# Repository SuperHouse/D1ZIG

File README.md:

D1 Mini Zigbee Shield
=====================

Zigbee shield for Wemos D1 Mini, so that it can either be a Zigbee
Client or a Zigbee Coordinator running Zigbee2Tasmota.

Features:

 * ESP8266 to run Zigbee2Tasmota
 * CC2530 Zigbee interface
 * 3D-printable case

More information is available at:

  https://www.superhouse.tv/d1zig

Hardware
--------
The "Hardware" directory contains the PCB design as an EAGLE project.
EAGLE PCB design software is available from Autodesk free for
non-commercial use.

Credits
-------
 * Jonathan Oxer <jon@oxer.com.au>

License
-------
Copyright 2020 SuperHouse Automation Pty Ltd  www.superhouse.tv  

The hardware portion of this project is licensed under the TAPR Open
Hardware License (www.tapr.org/OHL). The "license" folder within this
repository contains a copy of this license in plain text format.

The software portion of this project is licensed under the Simplified
BSD License. The "licence" folder within this project contains a
copy of this license in plain text format.

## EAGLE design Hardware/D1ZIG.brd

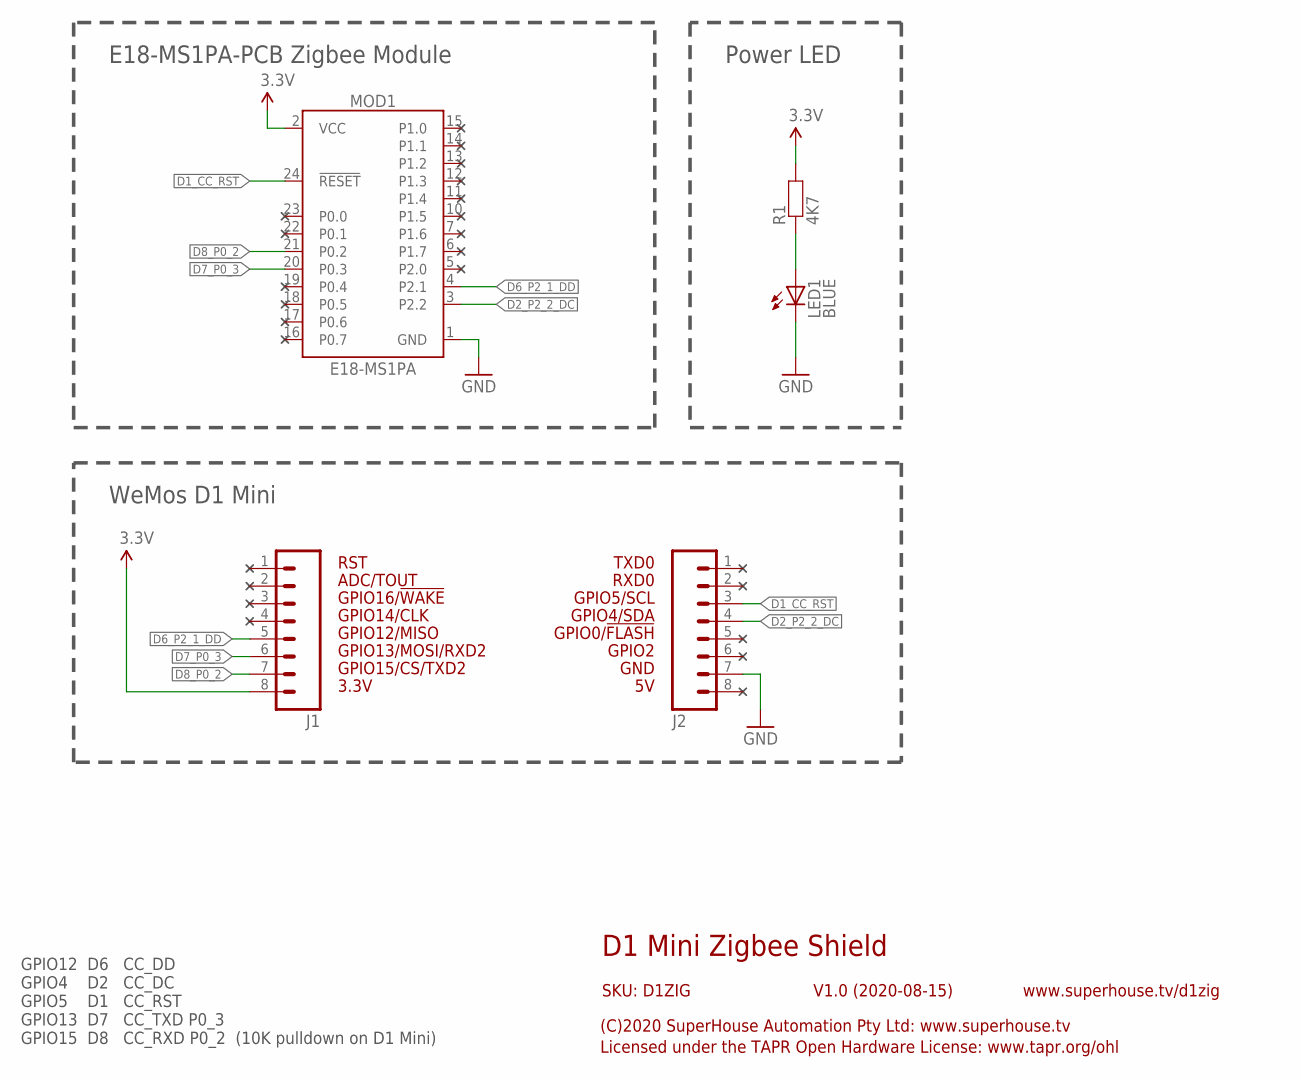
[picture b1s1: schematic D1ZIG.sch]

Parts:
J1, J2: M08; 1X08
LED1: BLUE; LED-0603
MOD1: E18-MS1PA; E18-MS1PA-PCB
R1: 4K7; R0603

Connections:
3.3V: J1.8, MOD1.2 (VCC), R1.2
D1_CC_RST: J2.3, MOD1.24 (!RESET)
D2_P2_2_DC: J2.4, MOD1.3 (P2.2)
D6_P2_1_DD: J1.5, MOD1.4 (P2.1)
D7_P0_3: J1.6, MOD1.20 (P0.3)
D8_P0_2: J1.7, MOD1.21 (P0.2)
GND: J2.7, LED1.C, MOD1.1 (GND)
unnamed: LED1.A, R1.1

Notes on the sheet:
GPIO2
GPIO0/!FLASH
GPIO12/MISO
GPIO4/SDA
GPIO5/SCL
RXD0
TXD0
GPIO13/MOSI/RXD2
GPIO14/CLK
GPIO15/CS/TXD2
GPIO16/!WAKE
ADC/TOUT
GPIO12 D6 CC_DD GPIO4 D2 CC_DC GPIO5 D1 CC_RST GPIO13 D7 CC_TXD P0_3 GPIO15 D8 CC_RXD P0_2 (10K pulldown on D1 Mini)
GND
3.3V
RST
E18-MS1PA-PCB Zigbee Module
WeMos D1 Mini
Power LED
D1 Mini Zigbee Shield
V1.0 (2020-08-15)
SKU: D1ZIG
(C)2020 SuperHouse Automation Pty Ltd: www.superhouse.tv
Licensed under the TAPR Open Hardware License: www.tapr.org/ohl
www.superhouse.tv/d1zig

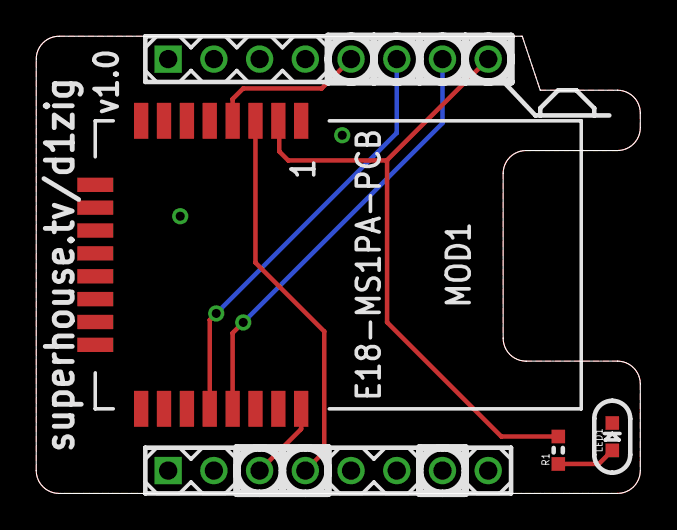
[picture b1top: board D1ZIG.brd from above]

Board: 2 copper layers, 33.6 x 25.4 mm, 5 parts (0 on the bottom side), 8 nets.

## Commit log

2020-08-13 Renamed PCB files to fork from Z2T
2020-08-13 Added module data
2020-08-14 Routing for v1.0 release
2020-08-15 Final DRC and tweaks for v1.0 release
2020-08-17 Flipped entire board for reverse mounting on D1 Mini for v1.0 release

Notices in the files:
parts and their libraries:
freetronics-original: Licensing: CC v3.0 Share-Alike You are welcome to use this library for commercial purposes.
